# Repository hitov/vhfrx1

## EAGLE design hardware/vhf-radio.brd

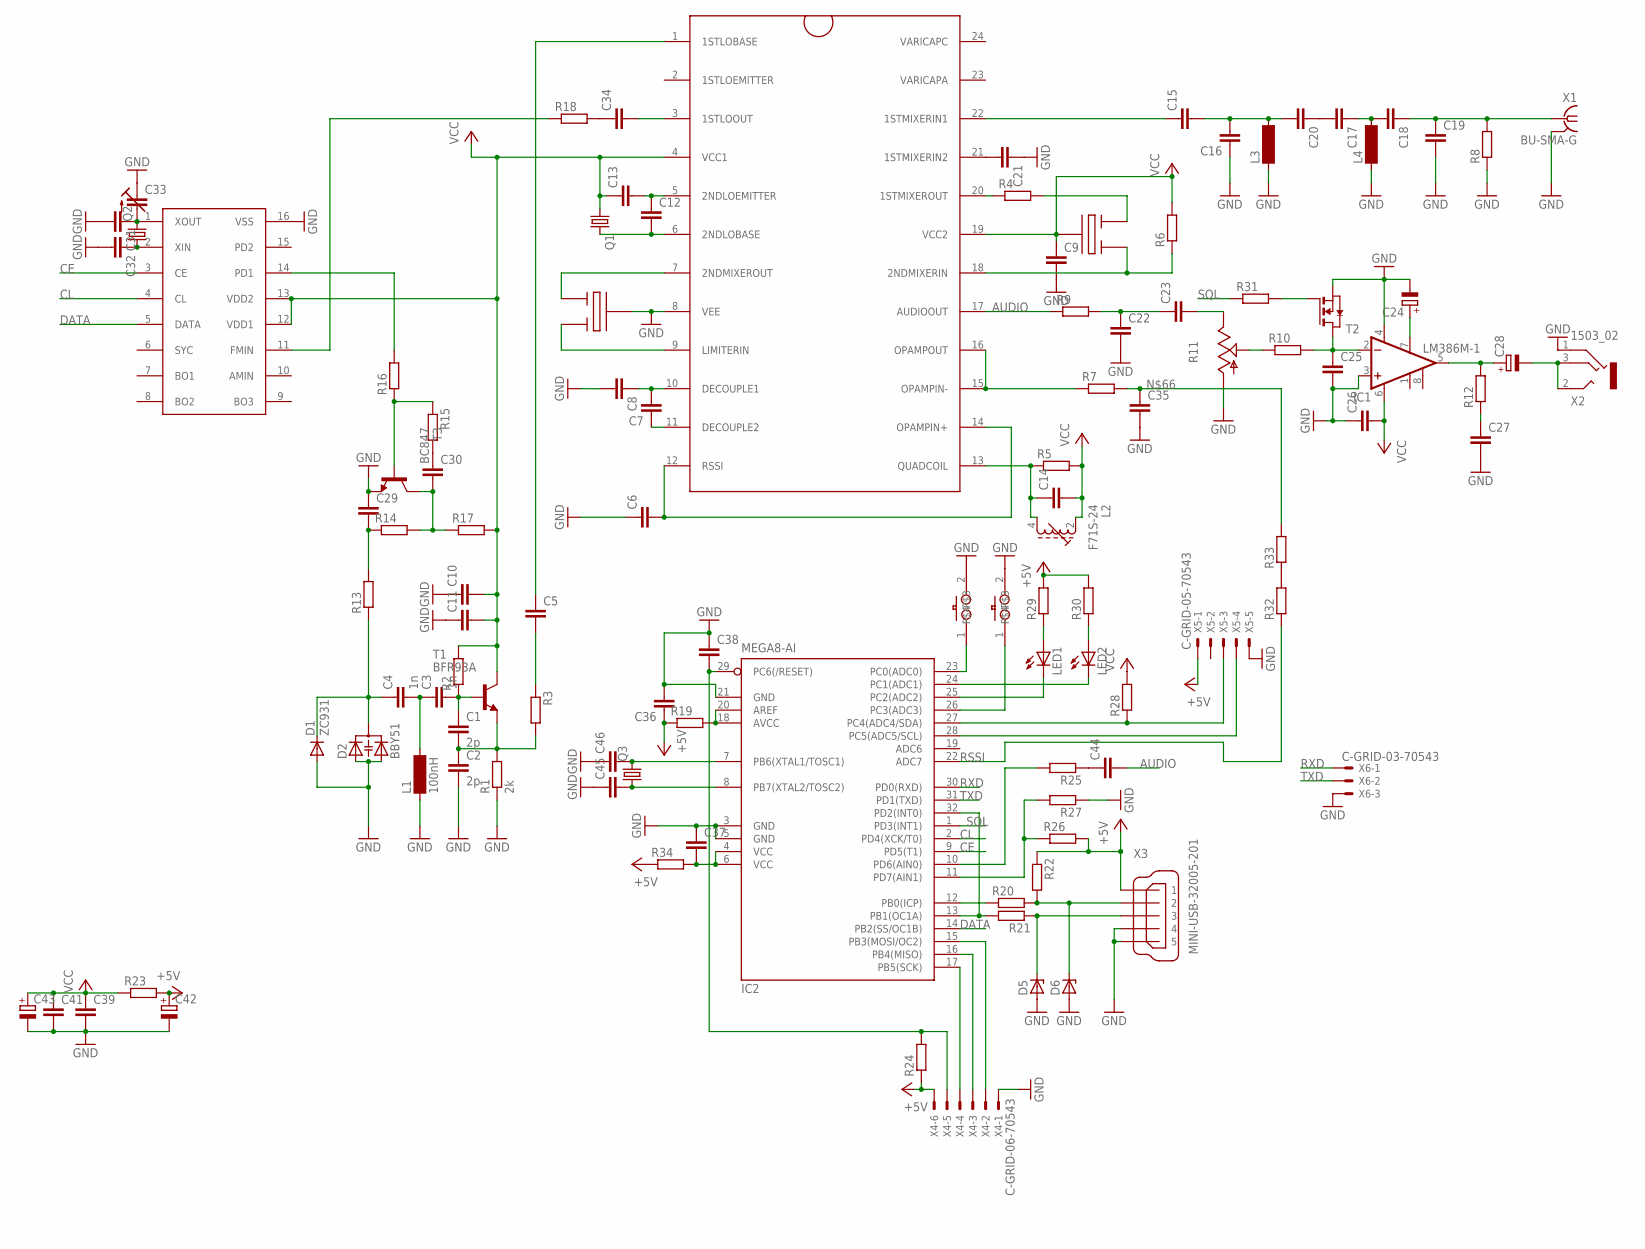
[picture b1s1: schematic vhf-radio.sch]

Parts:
C1, C2: 2p; C0805
C3, C4: 1n; C0805
C5, C6, C7, C8, C9, C10, C11, C12, C13, C14, C15, C16, C17, C18, C19, C20, C21, C22, C23, C25, C26, C27, C29, C30, C31, C32, C34, C35, C36, C37, C39, C41, C44, C45, C46: C-EUC0805; C0805
C24: CPOL-EU153CLV-0505; 153CLV-0505
C28: CPOL-EU153CLV-0605; 153CLV-0605
C33: C-TRIMM3018_12; CTRIM3018_12
C38: C-EU075-032X103; C075-032X103
C42, C43: CPOL-EU175TMP-0808; 175TMP-0808
D1: ZC931; MINIMELF
D2: BBY51; SOT23
D5, D6: ZENER-DIODESOD80C; SOD80C
IC1: LM386M-1; SO08
IC2: MEGA8-AI; TQFP32-08
L1: 100nH; SM-1206
L2: F71S-24; 71S
L3, L4: SM-1206
LED1, LED2: LEDCHIPLED_0805; CHIPLED_0805
Q1, Q2, Q3: CRYSTALHC49UP; HC49UP
R1: 2k; R0805
R2, R3, R4, R5, R6, R7, R8, R9, R10, R12, R13, R14, R15, R16, R17, R18, R19, R20, R21, R22, R24, R25, R26, R27, R29, R30: R-EU_R0805; R0805
R11: TRIM_US-CIP20C-6MM; CIP20C-6MM
R23, R28, R32, R33, R34: R-EU_0207/10; 0207/10
R31: R-EU_R1206; R1206
T1: BFR93A; SOT23-BEC
T2: NMOSSOT23; SOT-23
T3: BC847; SOT23
U$1: MC13135P-SMD; DIP-SMD
U$2, U$3: QFILTER; SIP3-SMD
U$4: LM7001-DIPSMD; DIP16-SMD
U$5, U$6: TS-1
X1: BU-SMA-G
X2: 1503_02
X3: MINI-USB-32005-201; 32005-201
X4: C-GRID-06-70543; 70543-06
X5: C-GRID-05-70543; 70543-05
X6: C-GRID-03-70543; 70543-03

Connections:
+5V: C36.1, C42.+, R19.1, R22.1, R23.2, R24.1, R26.2, R29.2, R30.2, R34.1, X3.1, X4.6, X5.1
AUDIO: C44.2, R9.1, U$1.17 (AUDIOOUT)
CE: IC2.9 (PD5(T1)), U$4.3 (CE)
CL: IC2.2 (PD4(XCK/T0)), U$4.4 (CL)
DATA: IC2.14 (PB2(SS/OC1B)), U$4.5 (DATA)
GND: C2.2, C6.1, C8.2, C9.2, C10.1, C11.1, C16.1, C19.2, C21.1, C22.2, C24.-, C25.2, C26.1, C27.2, C29.1, C31.2, C32.2, C33.+ (E), C35.2, C36.2, C37.1, C38.1, C39.2, C41.2, C42.-, C43.-, C45.1, C46.1, D1.A, D2.1 (A1), D2.2 (A2), D5.A, D6.A, IC1.3 (+IN), IC1.4 (GND), IC2.3 (GND), IC2.5 (GND), IC2.21 (GND), L1.1, L3.1, L4.1, R1.1, R8.1, R11.A, R27.1, T2.2 (S), T3.2 (E), U$1.8 (VEE), U$2.P$2 (2), U$4.16 (VSS), U$5.2, U$6.2, X1.2 (GND), X1.3 (GND), X1.4 (GND), X1.5 (GND), X2.1, X3.4, X3.5, X4.1, X5.5, X6.3
unnamed: C1.2, C2.1, R1.2, R3.2, T1.E
unnamed: C1.1, C3.2, R2.1, T1.B
unnamed: C5.2, R3.1
unnamed: C3.1, C4.2, L1.2
unnamed: R16.2, U$4.14 (PD1)
unnamed: C5.1, U$1.1 (1STLOBASE)
unnamed: C6.2, U$1.12 (RSSI), U$1.14 (OPAMPIN+)
unnamed: U$1.7 (2NDMIXEROUT), U$2.P$1 (1)
unnamed: U$1.9 (LIMITERIN), U$2.P$3 (3)
unnamed: C14.1, L2.4 (E), R5.1, U$1.13 (QUADCOIL)
unnamed: C12.2, Q1.2, U$1.6 (2NDLOBASE)
unnamed: R4.1, U$1.20 (1STMIXEROUT)
unnamed: R4.2, U$3.P$3 (3)
unnamed: R6.1, U$1.18 (2NDMIXERIN), U$3.P$1 (1)
unnamed: C12.1, C13.2, U$1.5 (2NDLOEMITTER)
unnamed: C15.2, C16.2, C20.2, L3.2
unnamed: C7.1, U$1.11 (DECOUPLE2)
unnamed: C7.2, C8.1, U$1.10 (DECOUPLE1)
unnamed: R7.1, U$1.15 (OPAMPIN-), U$1.16 (OPAMPOUT)
unnamed: C21.2, U$1.21 (1STMIXERIN2)
unnamed: C15.1, U$1.22 (1STMIXERIN1)
unnamed: C45.2, IC2.8 (PB7(XTAL2/TOSC2)), Q3.1
unnamed: C17.2, C20.1
unnamed: C17.1, C18.2, L4.2
unnamed: C18.1, C19.1, R8.2, X1.1
unnamed: C22.1, C23.1, R9.2
unnamed: C23.2, R11.E
unnamed: R10.1, R11.S
unnamed: C25.1, IC1.2 (-IN), R10.2, T2.1 (D)
unnamed: C24.+, IC1.7 (BYPASS)
unnamed: C29.2, R13.2, R14.1
unnamed: C27.1, R12.1
unnamed: C28.+, IC1.5 (OUT), R12.2
unnamed: C28.-, X2.2, X2.3
unnamed: C30.2, R14.2, R17.1, T3.3 (C)
unnamed: R15.1, R16.1, T3.1 (B)
unnamed: C30.1, R15.2
unnamed: C31.1, C33.- (A), Q2.2, U$4.1 (XOUT)
unnamed: IC2.18 (AVCC), IC2.20 (AREF), R19.2
unnamed: C32.1, Q2.1, U$4.2 (XIN)
unnamed: C34.1, R18.2
unnamed: C34.2, U$1.3 (1STLOOUT)
unnamed: R18.1, U$4.11 (FMIN)
unnamed: C4.1, D1.C, D2.3 (C), R13.1
unnamed: IC2.13 (PB1(OC1A)), IC2.32 (PD2(INT0)), R21.2
unnamed: IC2.12 (PB0(ICP)), R20.1
unnamed: D6.C, R20.2, R22.2, X3.2
unnamed: D5.C, R21.1, X3.3
unnamed: IC2.15 (PB3(MOSI/OC2)), X4.2
unnamed: IC2.16 (PB4(MISO)), X4.3
unnamed: IC2.17 (PB5(SCK)), X4.4
unnamed: C38.2, IC2.29 (PC6(/RESET)), R24.2, X4.5
unnamed: C44.1, R25.1
unnamed: IC2.10 (PD6(AIN0)), R25.2
unnamed: IC2.11 (PD7(AIN1)), R26.1, R27.2
unnamed: C46.2, IC2.7 (PB6(XTAL1/TOSC1)), Q3.2
unnamed: IC2.27 (PC4(ADC4/SDA)), R28.1, X5.3
unnamed: IC2.28 (PC5(ADC5/SCL)), X5.4
unnamed: IC2.25 (PC2(ADC2)), LED1.C
unnamed: IC2.24 (PC1(ADC1)), LED2.C
unnamed: LED1.A, R29.1
unnamed: LED2.A, R30.1
unnamed: IC2.23 (PC0(ADC0)), U$5.1
unnamed: IC2.26 (PC3(ADC3)), U$6.1
unnamed: R31.2, T2.3 (G)
unnamed: C35.1, R7.2, R33.2
unnamed: R32.2, R33.1
unnamed: C37.2, IC2.4 (VCC), IC2.6 (VCC), R34.2
RSSI: IC2.22 (ADC7), R32.1
RXD: IC2.30 (PD0(RXD)), X6.1
SQL: IC2.1 (PD3(INT1)), R31.1
TXD: IC2.31 (PD1(TXD)), X6.2
VCC: C9.1, C10.2, C11.2, C13.1, C14.2, C26.2, C39.1, C41.1, C43.+, IC1.6 (VS), L2.2 (A), Q1.1, R2.2, R5.2, R6.2, R17.2, R23.1, R28.2, T1.C, U$1.4 (VCC1), U$1.19 (VCC2), U$3.P$2 (2), U$4.12 (VDD1), U$4.13 (VDD2)

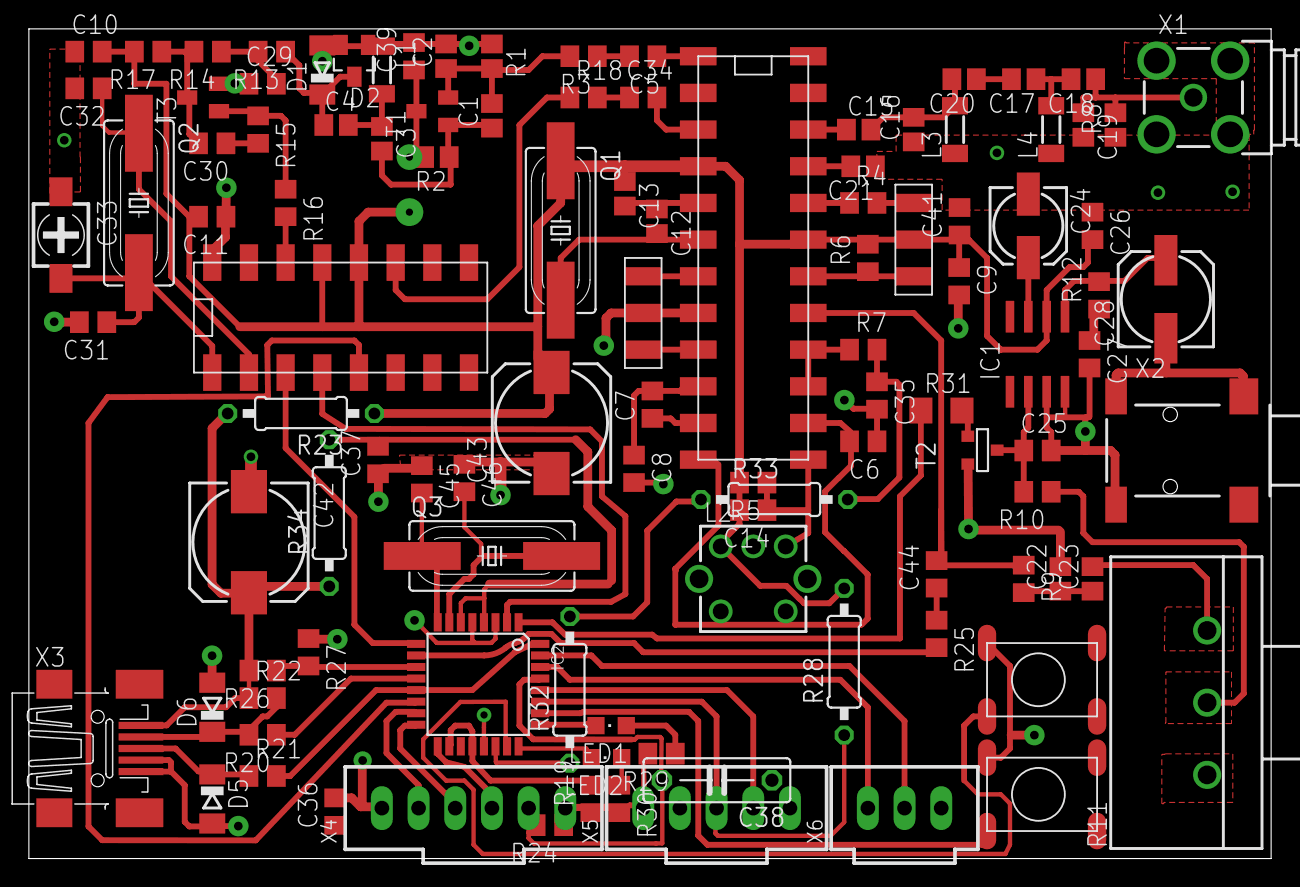
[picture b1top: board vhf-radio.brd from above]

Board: 2 copper layers, 86.0 x 57.5 mm, 109 parts (0 on the bottom side), 79 nets.

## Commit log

2013-01-09 VHF Radio - Initial commit
2013-01-09 Add .gitignore
2013-01-09 LEDS On
2013-01-09 Make Leds to blink
2013-05-11 Add lm7001 driver (initial non tested)
2013-05-11 LM7001 driver update and build conditions
2013-05-18 Add LTspice VCO simulation
2013-05-26 [HW] New schematics for aprs tracker
2013-05-27 [HW] Update schematics
2013-05-31 [HW] Schematic update
2013-05-31 [HW] Kicad project adjustments
2013-06-03 [HW] Schematics/footprints update
2013-06-04 [HW] Update pcb, rearrange components
2013-11-24 [HW] Add uncommited changes / PCB updates
2013-11-24 [HW] route pcb
2013-11-27 [HW] PCB Ground plane update
2013-11-30 [HW] Fix GPS footprint and pcb
2013-11-30 [HW] PCB - rearrange designators
2013-11-30 [HW] PCB - minor adjustments
2013-11-30 [HW] PCB - Fix DRC errors
2013-12-02 [HW] Update pcb/sch/gps
2013-12-02 [HW] remove aprs.bak
2013-12-03 [HW] Add schematics values
2013-12-03 [HW] Update schematics element values, add .gitignore rules, add files
2013-12-08 [HW] - Fix schematics of collpits oscillator and add values
2013-12-15 [HW] Update schematic elements values
2013-12-15 [HW] Update values. Add capacitor to suppress negative feedback
2013-12-15 [HW] Add simulations for vco an tx
2014-01-04 Update sch elements values
2014-01-04 [HW] Generate schematics pdf file
2014-01-04 [HW] Fix element values
